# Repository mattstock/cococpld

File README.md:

cococpld
========

A complete bus interface design for the Tandy Color Computer for Arduino/AVR!

This is a combined open source/open hardware project to design a development board the Tandy/TRS-80 Color Computer.

Directories:

firmware2 - AVR Studio 6 project for a simple ROM programmer for the board.
cpld - Altera Quartus project to implement the control logic for the board.
kicad - Kicad project including the schematics and board layout.

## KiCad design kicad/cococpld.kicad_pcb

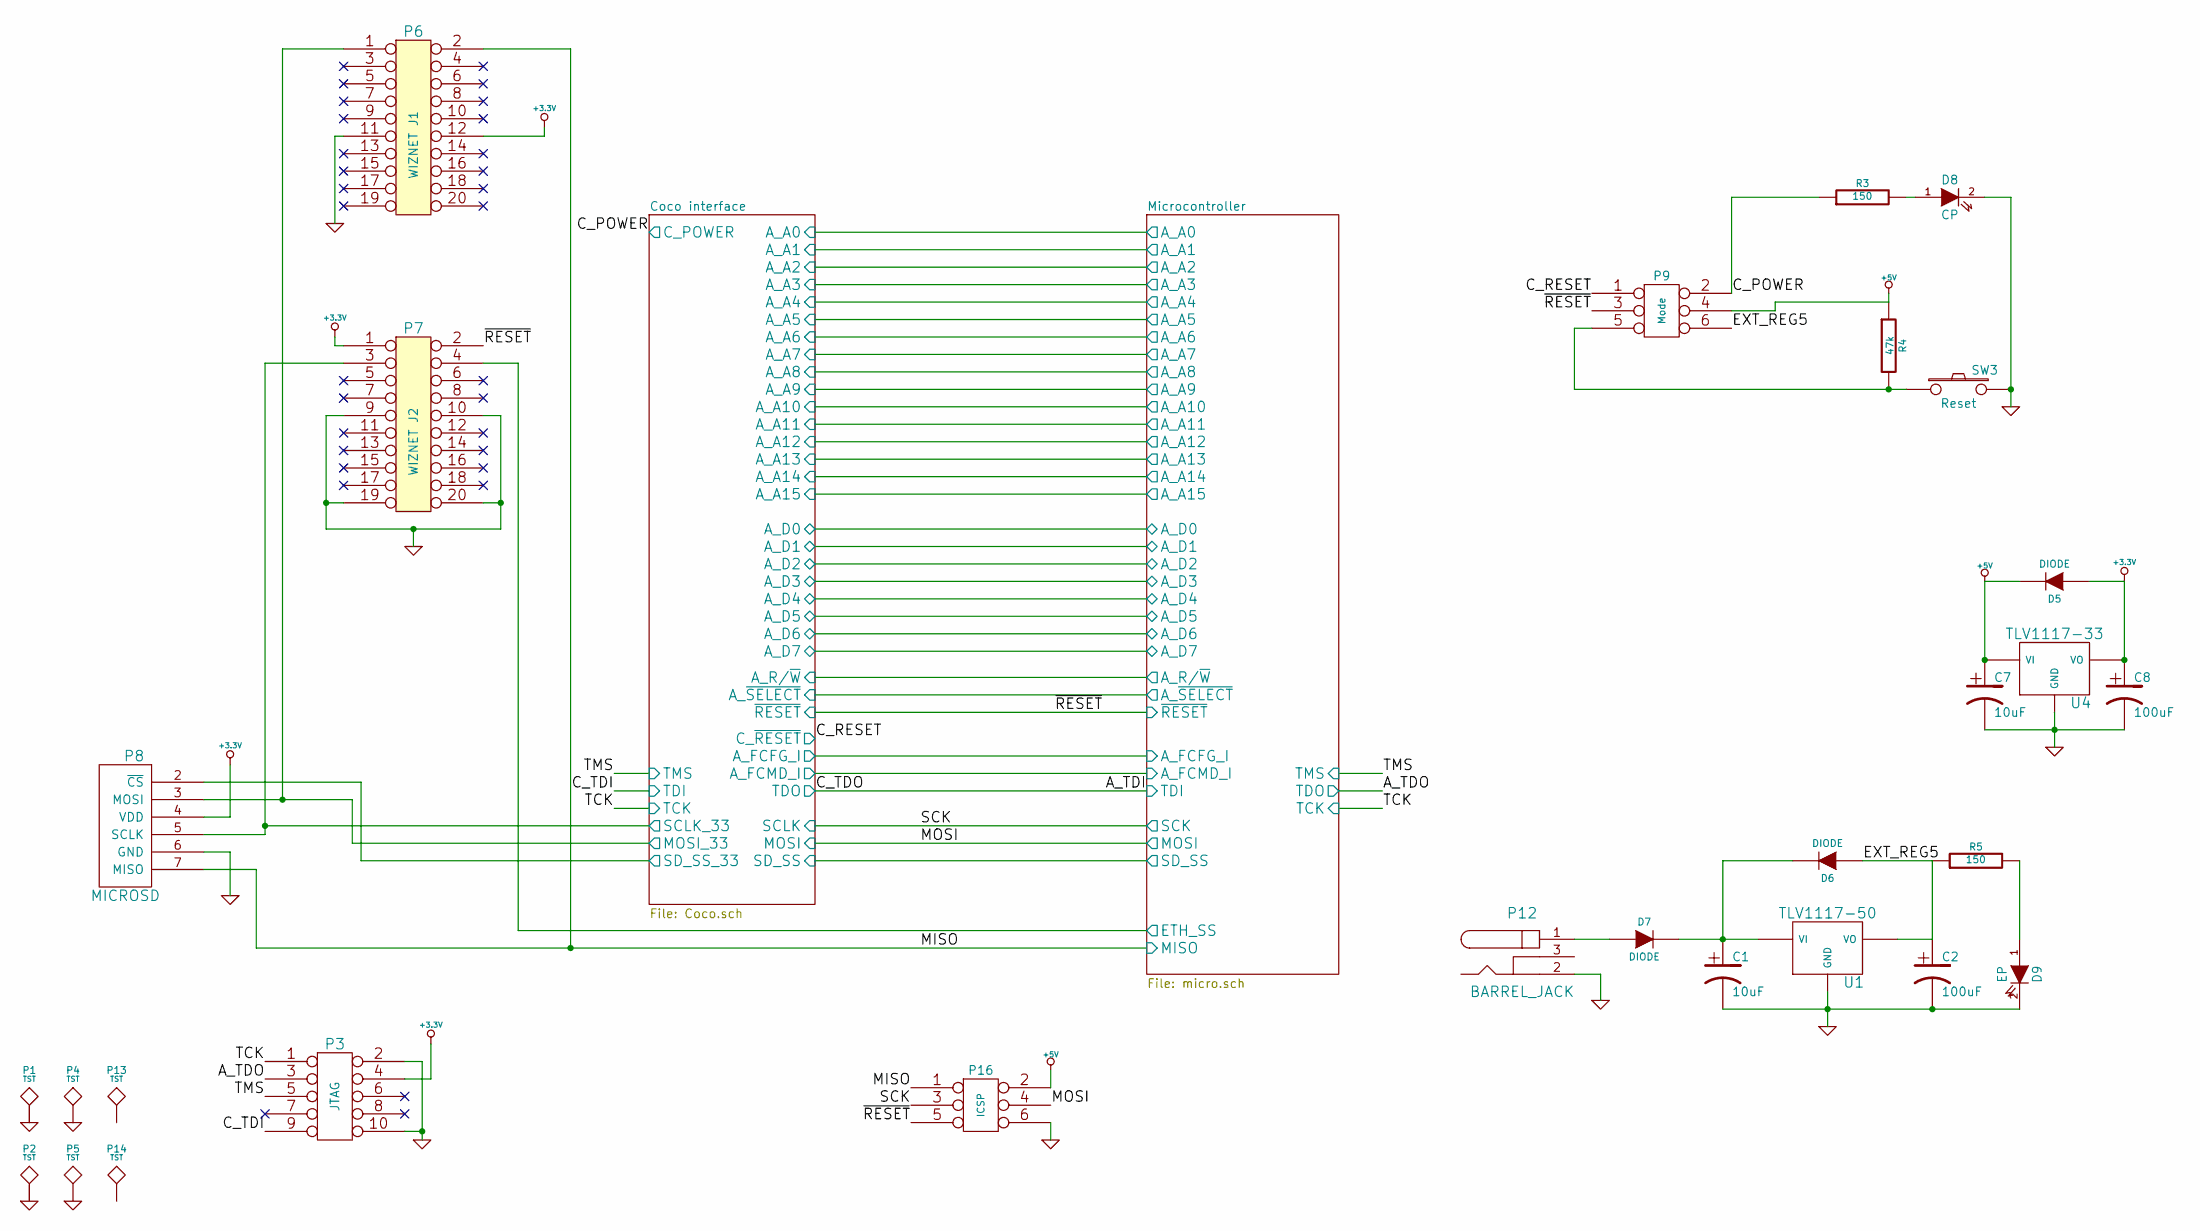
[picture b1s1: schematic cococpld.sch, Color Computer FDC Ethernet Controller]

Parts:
C1, C7: 10uF
C2, C8: 100uF
D5, D6, D7: DIODE
D8: CP
D9: EP
P1, P2, P4, P5, P13, P14: TST
P3: JTAG
P6: WIZNET J1
P7: WIZNET J2
P8: MICROSD
P9: Mode
P12: BARREL_JACK
P16: ICSP
R3, R5: 150
R4: 47k
SW3: Reset
U1: TLV1117-50
U4: TLV1117-33

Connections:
+3.3V: C8.1, D5.1 (A), P3.4, P6.12, P7.1, P8.4 (VDD), U4.2 (VO); also elsewhere on the board
+5V: C7.1, D5.2 (K), P9.4, P16.2, R4.1, U4.3 (VI); also elsewhere on the board
/Coco interface/C_POWER: P9.2, R3.1; also elsewhere on the board
/Coco interface/C_~RESET: P9.1; also elsewhere on the board
/Coco interface/MOSI: P16.4; also elsewhere on the board
/Coco interface/MOSI_33: P6.1, P8.3 (MOSI); also elsewhere on the board
/Coco interface/SCLK_33: P7.3, P8.5 (SCLK); also elsewhere on the board
/Coco interface/SD_SS_33: P8.2 (~CS); also elsewhere on the board
/Coco interface/TCK: P3.1; also elsewhere on the board
/Coco interface/TDI: P3.9; also elsewhere on the board
/Coco interface/TMS: P3.5; also elsewhere on the board
/Coco interface/~RESET: P7.2, P9.3, P16.5; also elsewhere on the board
/EXT_REG5: C2.1, D6.1 (A), P9.6, R5.1, U1.2 (VO)
/Microcontroller/ETH_SS: P7.4; also elsewhere on the board
/Microcontroller/MISO: P6.2, P8.7 (MISO), P16.1; also elsewhere on the board
/Microcontroller/SCK: P16.3; also elsewhere on the board
/Microcontroller/TDO: P3.3; also elsewhere on the board
GND: C1.2, C2.2, C7.2, C8.2, D8.2 (K), D9.2 (K), P1.1, P2.1, P3.2, P3.10, P4.1, P5.1, P6.11, P7.9, P7.10, P7.19, P7.20, P8.6 (GND), P12.2, P16.6, SW3.2, U1.1 (GND), U4.1 (GND); also elsewhere on the board
unnamed: C1.1, D6.2 (K), D7.2 (K), U1.3 (VI)
unnamed: D7.1 (A), P12.1
unnamed: D9.1 (A), R5.2
unnamed: D8.1 (A), R3.2
unnamed: P9.5, R4.2, SW3.1

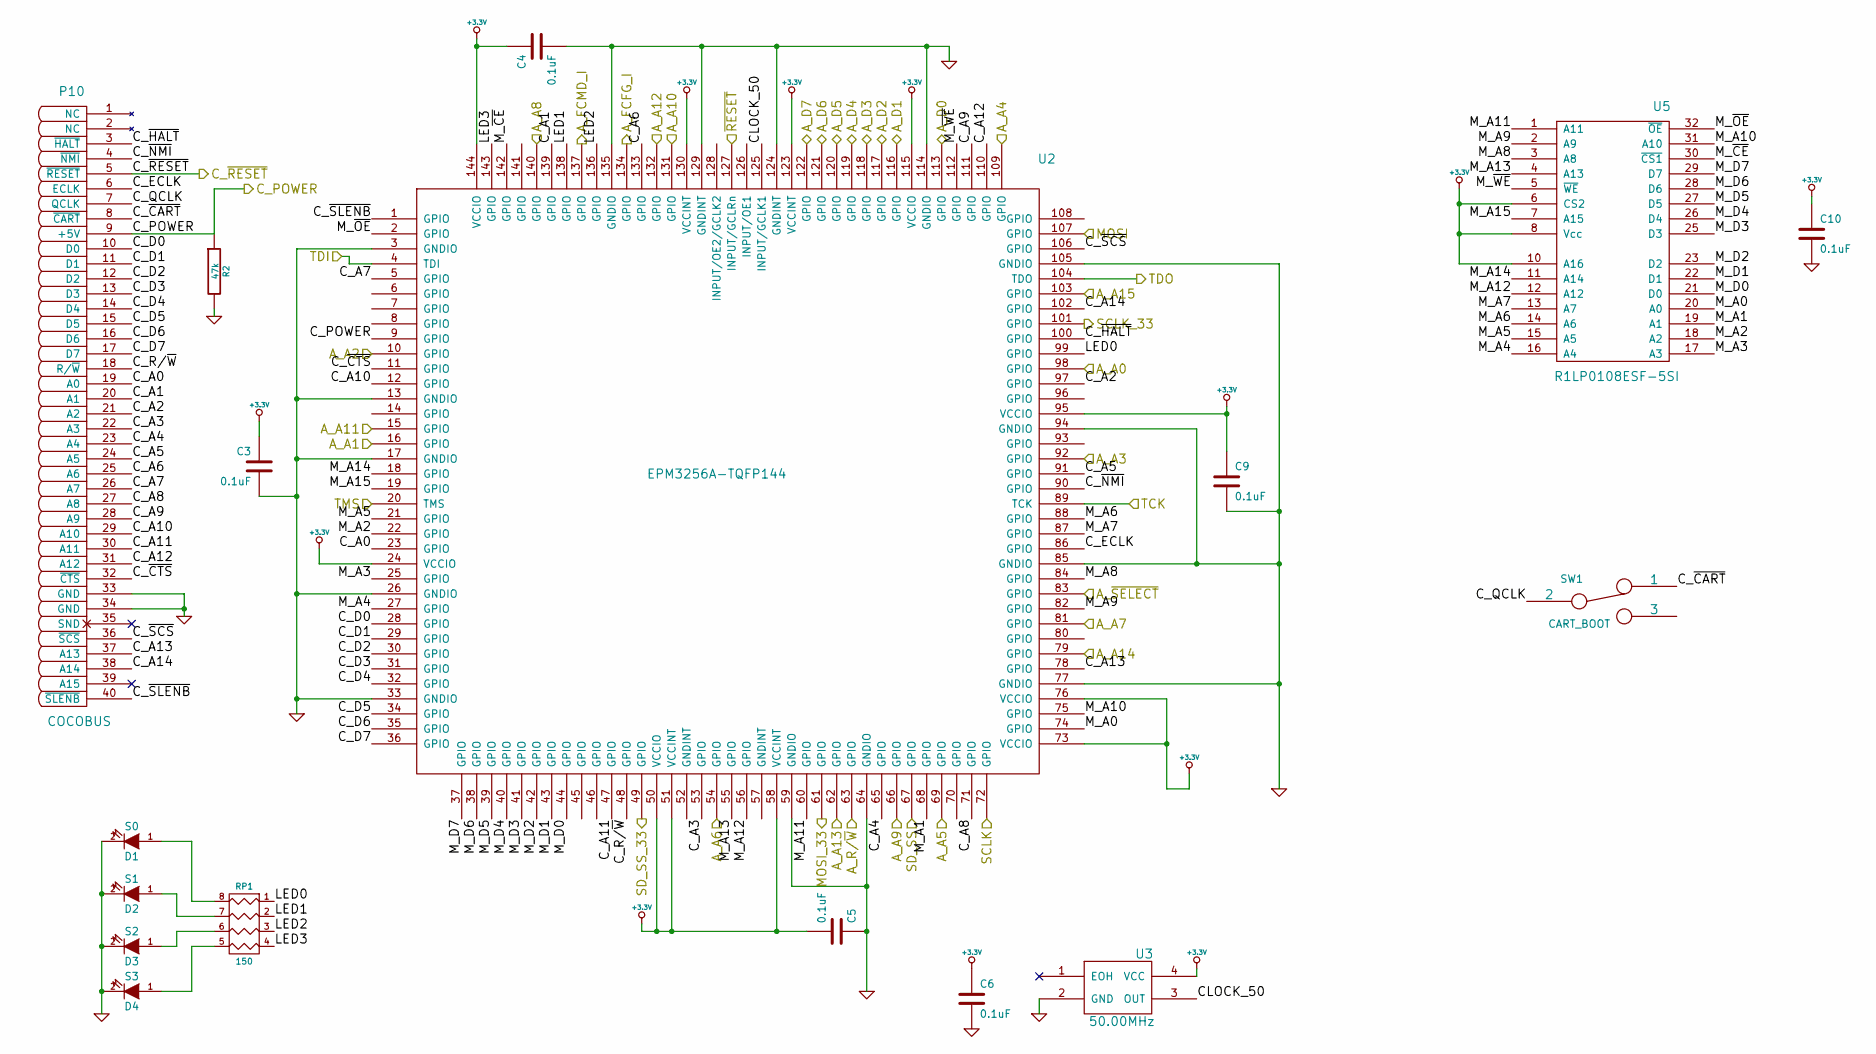
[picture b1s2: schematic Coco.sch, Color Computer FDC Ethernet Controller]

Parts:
C3, C4, C5, C6, C9, C10: 0.1uF
D1: S0
D2: S1
D3: S2
D4: S3
P10: COCOBUS
R2: 47k
RP1: 150
SW1: CART_BOOT
U2: EPM3256A-TQFP144
U3: 50.00MHz
U5: R1LP0108ESF-5SI

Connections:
+3.3V: C3.1, C4.1, C5.2, C6.1, C9.1, C10.1, U2.24 (VCCIO), U2.50 (VCCIO), U2.51 (VCCINT), U2.58 (VCCINT), U2.73 (VCCIO), U2.76 (VCCIO), U2.95 (VCCIO), U2.115 (VCCIO), U2.123 (VCCINT), U2.130 (VCCINT), U2.144 (VCCIO), U3.4 (VCC), U5.6 (CS2), U5.8 (Vcc), U5.10 (A16); also elsewhere on the board
/Coco interface/A_A0: U2.98 (GPIO); also elsewhere on the board
/Coco interface/A_A1: U2.16 (GPIO); also elsewhere on the board
/Coco interface/A_A2: U2.10 (GPIO); also elsewhere on the board
/Coco interface/A_A3: U2.92 (GPIO); also elsewhere on the board
/Coco interface/A_A4: U2.109 (GPIO); also elsewhere on the board
/Coco interface/A_A5: U2.69 (GPIO); also elsewhere on the board
/Coco interface/A_A6: U2.54 (GPIO); also elsewhere on the board
/Coco interface/A_A7: U2.81 (GPIO); also elsewhere on the board
/Coco interface/A_A8: U2.140 (GPIO); also elsewhere on the board
/Coco interface/A_A9: U2.66 (GPIO); also elsewhere on the board
/Coco interface/A_A10: U2.131 (GPIO); also elsewhere on the board
/Coco interface/A_A11: U2.15 (GPIO); also elsewhere on the board
/Coco interface/A_A12: U2.132 (GPIO); also elsewhere on the board
/Coco interface/A_A13: U2.62 (GPIO); also elsewhere on the board
/Coco interface/A_A14: U2.79 (GPIO); also elsewhere on the board
/Coco interface/A_A15: U2.103 (GPIO); also elsewhere on the board
/Coco interface/A_D0: U2.113 (GPIO); also elsewhere on the board
/Coco interface/A_D1: U2.116 (GPIO); also elsewhere on the board
/Coco interface/A_D2: U2.117 (GPIO); also elsewhere on the board
/Coco interface/A_D3: U2.118 (GPIO); also elsewhere on the board
/Coco interface/A_D4: U2.119 (GPIO); also elsewhere on the board
/Coco interface/A_D5: U2.120 (GPIO); also elsewhere on the board
/Coco interface/A_D6: U2.121 (GPIO); also elsewhere on the board
/Coco interface/A_D7: U2.122 (GPIO); also elsewhere on the board
/Coco interface/A_FCFG_I: U2.134 (GPIO); also elsewhere on the board
/Coco interface/A_FCMD_I: U2.137 (GPIO); also elsewhere on the board
/Coco interface/A_R/~W: U2.63 (GPIO); also elsewhere on the board
/Coco interface/A_~SELECT: U2.83 (GPIO); also elsewhere on the board
/Coco interface/CLOCK_50: U2.125 (INPUT/GCLK1), U3.3 (OUT)
/Coco interface/C_A0: P10.19 (A0), U2.23 (GPIO)
/Coco interface/C_A1: P10.20 (A1), U2.139 (GPIO)
/Coco interface/C_A2: P10.21 (A2), U2.97 (GPIO)
/Coco interface/C_A3: P10.22 (A3), U2.53 (GPIO)
/Coco interface/C_A4: P10.23 (A4), U2.65 (GPIO)
/Coco interface/C_A5: P10.24 (A5), U2.91 (GPIO)
/Coco interface/C_A6: P10.25 (A6), U2.133 (GPIO)
/Coco interface/C_A7: P10.26 (A7), U2.5 (GPIO)
/Coco interface/C_A8: P10.27 (A8), U2.71 (GPIO)
/Coco interface/C_A9: P10.28 (A9), U2.111 (GPIO)
/Coco interface/C_A10: P10.29 (A10), U2.12 (GPIO)
/Coco interface/C_A11: P10.30 (A11), U2.47 (GPIO)
/Coco interface/C_A12: P10.31 (A12), U2.110 (GPIO)
/Coco interface/C_A13: P10.37 (A13), U2.78 (GPIO)
/Coco interface/C_A14: P10.38 (A14), U2.102 (GPIO)
/Coco interface/C_D0: P10.10 (D0), U2.28 (GPIO)
/Coco interface/C_D1: P10.11 (D1), U2.29 (GPIO)
/Coco interface/C_D2: P10.12 (D2), U2.30 (GPIO)
/Coco interface/C_D3: P10.13 (D3), U2.31 (GPIO)
/Coco interface/C_D4: P10.14 (D4), U2.32 (GPIO)
/Coco interface/C_D5: P10.15 (D5), U2.34 (GPIO)
/Coco interface/C_D6: P10.16 (D6), U2.35 (GPIO)
/Coco interface/C_D7: P10.17 (D7), U2.36 (GPIO)
/Coco interface/C_ECLK: P10.6 (ECLK), U2.86 (GPIO)
/Coco interface/C_POWER: P10.9 (+5V), R2.1, U2.9 (GPIO); also elsewhere on the board
/Coco interface/C_QCLK: P10.7 (QCLK), SW1.2
/Coco interface/C_R/~W: P10.18 (R/~W), U2.48 (GPIO)
/Coco interface/C_~CART: P10.8 (~CART), SW1.1
/Coco interface/C_~CTS: P10.32 (~CTS), U2.11 (GPIO)
/Coco interface/C_~HALT: P10.3 (~HALT), U2.100 (GPIO)
/Coco interface/C_~NMI: P10.4 (~NMI), U2.90 (GPIO)
/Coco interface/C_~RESET: P10.5 (~RESET); also elsewhere on the board
/Coco interface/C_~SCS: P10.36 (~SCS), U2.106 (GPIO)
/Coco interface/C_~SLENB: P10.40 (~SLENB), U2.1 (GPIO)
/Coco interface/LED0: RP1.1, U2.99 (GPIO)
/Coco interface/LED1: RP1.2, U2.138 (GPIO)
/Coco interface/LED2: RP1.3, U2.136 (GPIO)
/Coco interface/LED3: RP1.4, U2.143 (GPIO)
/Coco interface/MOSI: U2.107 (GPIO); also elsewhere on the board
/Coco interface/MOSI_33: U2.61 (GPIO); also elsewhere on the board
/Coco interface/M_A0: U2.74 (GPIO), U5.20 (A0)
/Coco interface/M_A1: U2.68 (GPIO), U5.19 (A1)
/Coco interface/M_A2: U2.22 (GPIO), U5.18 (A2)
/Coco interface/M_A3: U2.25 (GPIO), U5.17 (A3)
/Coco interface/M_A4: U2.27 (GPIO), U5.16 (A4)
/Coco interface/M_A5: U2.21 (GPIO), U5.15 (A5)
/Coco interface/M_A6: U2.88 (GPIO), U5.14 (A6)
/Coco interface/M_A7: U2.87 (GPIO), U5.13 (A7)
/Coco interface/M_A8: U2.84 (GPIO), U5.3 (A8)
/Coco interface/M_A9: U2.82 (GPIO), U5.2 (A9)
/Coco interface/M_A10: U2.75 (GPIO), U5.31 (A10)
/Coco interface/M_A11: U2.60 (GPIO), U5.1 (A11)
/Coco interface/M_A12: U2.56 (GPIO), U5.12 (A12)
/Coco interface/M_A13: U2.55 (GPIO), U5.4 (A13)
/Coco interface/M_A14: U2.18 (GPIO), U5.11 (A14)
/Coco interface/M_A15: U2.19 (GPIO), U5.7 (A15)
/Coco interface/M_D0: U2.44 (GPIO), U5.21 (D0)
/Coco interface/M_D1: U2.43 (GPIO), U5.22 (D1)
/Coco interface/M_D2: U2.42 (GPIO), U5.23 (D2)
/Coco interface/M_D3: U2.41 (GPIO), U5.25 (D3)
/Coco interface/M_D4: U2.40 (GPIO), U5.26 (D4)
/Coco interface/M_D5: U2.39 (GPIO), U5.27 (D5)
/Coco interface/M_D6: U2.38 (GPIO), U5.28 (D6)
/Coco interface/M_D7: U2.37 (GPIO), U5.29 (D7)
/Coco interface/M_~CE: U2.142 (GPIO), U5.30 (~CS1)
/Coco interface/M_~OE: U2.2 (GPIO), U5.32 (~OE)
/Coco interface/M_~WE: U2.112 (GPIO), U5.5 (~WE)
/Coco interface/SCLK_33: U2.101 (GPIO); also elsewhere on the board
/Coco interface/SD_SS: U2.67 (GPIO); also elsewhere on the board
/Coco interface/SD_SS_33: U2.49 (GPIO); also elsewhere on the board
/Coco interface/TCK: U2.89 (TCK); also elsewhere on the board
/Coco interface/TDI: U2.4 (TDI); also elsewhere on the board
/Coco interface/TMS: U2.20 (TMS); also elsewhere on the board
/Coco interface/~RESET: U2.127 (INPUT/GCLRn); also elsewhere on the board
/Microcontroller/SCK: U2.72 (GPIO); also elsewhere on the board
/Microcontroller/TDI: U2.104 (TDO); also elsewhere on the board
GND: C3.2, C4.2, C5.1, C6.2, C9.2, C10.2, D1.2 (K), D2.2 (K), D3.2 (K), D4.2 (K), P10.33 (GND), P10.34 (GND), R2.2, U2.3 (GNDIO), U2.13 (GNDIO), U2.17 (GNDIO), U2.26 (GNDIO), U2.33 (GNDIO), U2.59 (GNDIO), U2.64 (GNDIO), U2.77 (GNDIO), U2.85 (GNDIO), U2.94 (GNDIO), U2.105 (GNDIO), U2.114 (GNDIO), U2.124 (GNDINT), U2.129 (GNDINT), U2.135 (GNDIO), U3.2 (GND), U5.24 (GND); also elsewhere on the board
unnamed: D3.1 (A), RP1.6 (R3)
unnamed: D1.1 (A), RP1.8 (R1)
unnamed: D4.1 (A), RP1.5 (R4)
unnamed: D2.1 (A), RP1.7 (R2)

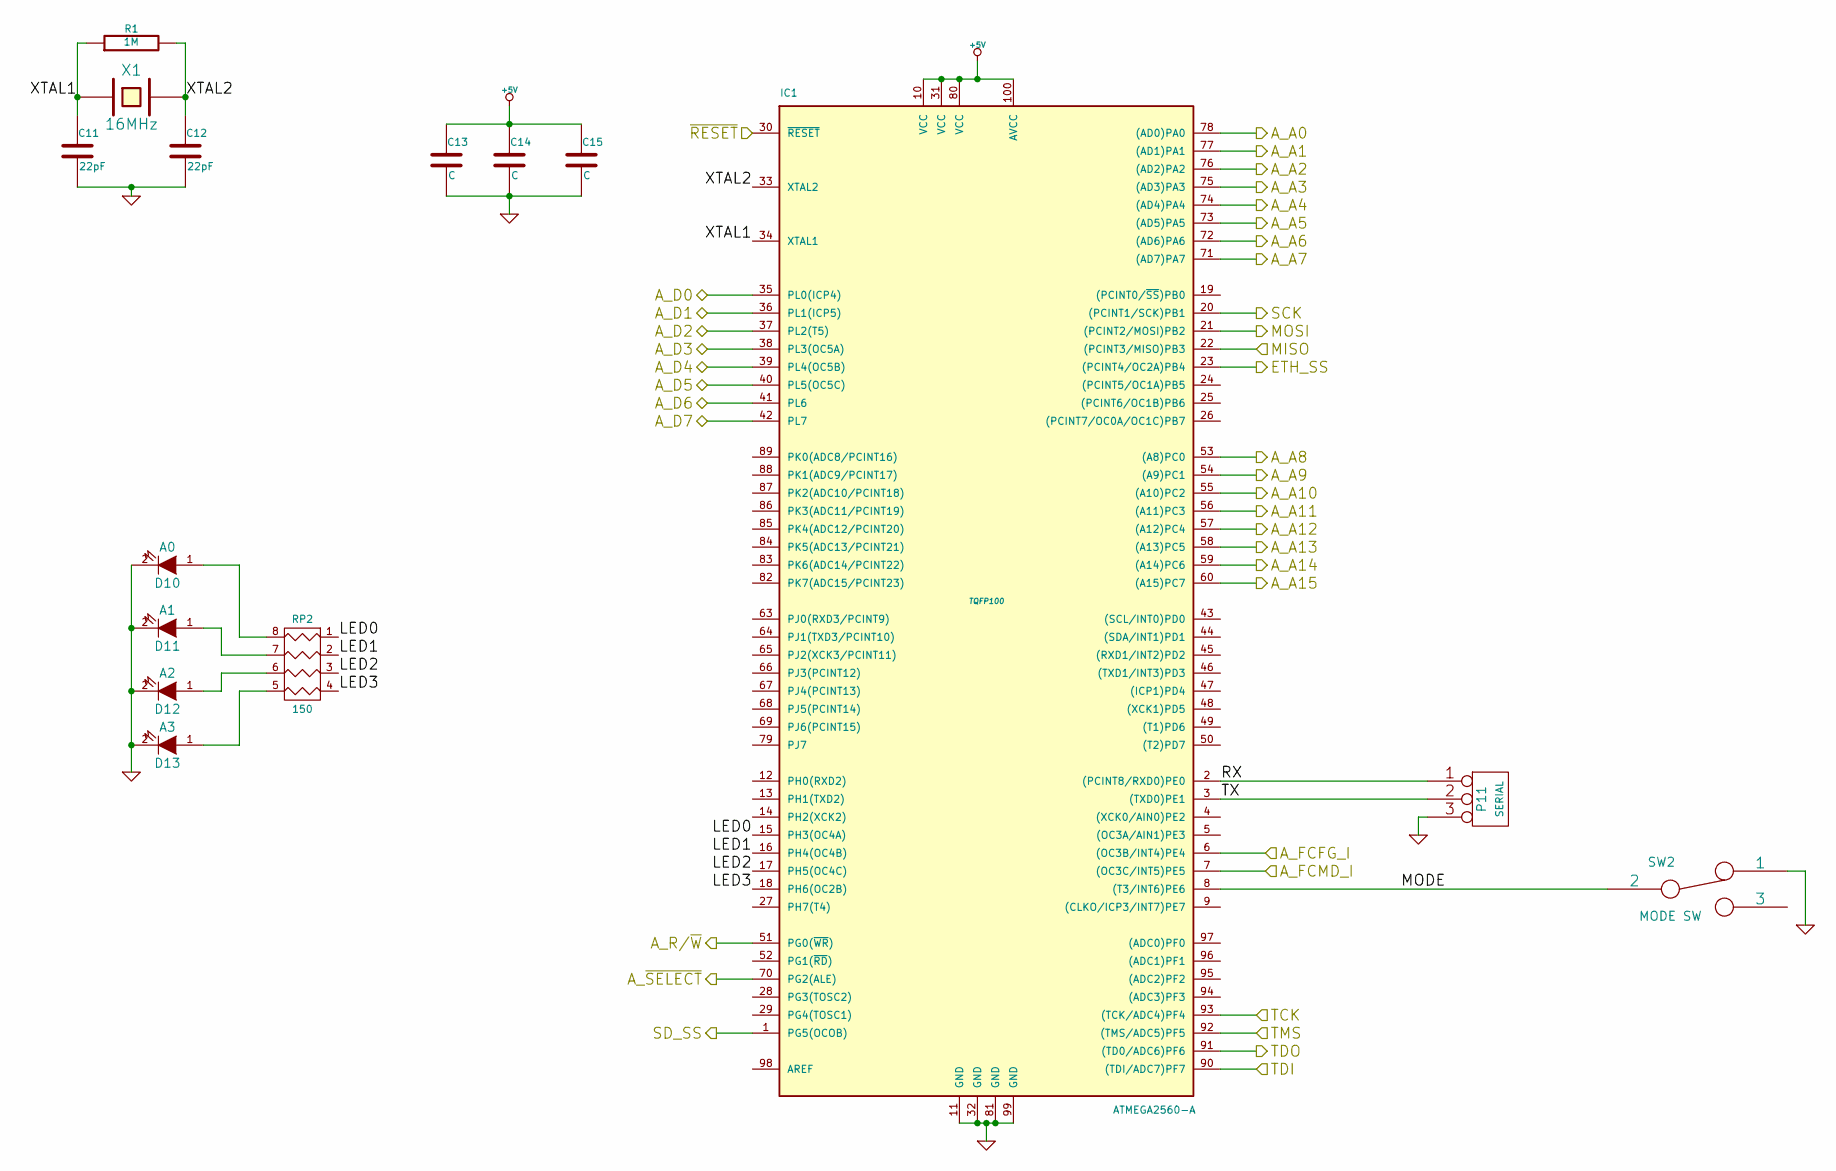
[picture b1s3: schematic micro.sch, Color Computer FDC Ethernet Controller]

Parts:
C11, C12: 22pF
C13, C14, C15: C
D10: A0
D11: A1
D12: A2
D13: A3
IC1: ATMEGA2560-A; TQFP100
P11: SERIAL
R1: 1M
RP2: 150
SW2: MODE SW
X1: 16MHz

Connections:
+5V: C13.1, C14.1, C15.1, IC1.10 (VCC), IC1.31 (VCC), IC1.80 (VCC), IC1.100 (AVCC); also elsewhere on the board
/Coco interface/A_A0: IC1.78 ((AD0)PA0); also elsewhere on the board
/Coco interface/A_A1: IC1.77 ((AD1)PA1); also elsewhere on the board
/Coco interface/A_A2: IC1.76 ((AD2)PA2); also elsewhere on the board
/Coco interface/A_A3: IC1.75 ((AD3)PA3); also elsewhere on the board
/Coco interface/A_A4: IC1.74 ((AD4)PA4); also elsewhere on the board
/Coco interface/A_A5: IC1.73 ((AD5)PA5); also elsewhere on the board
/Coco interface/A_A6: IC1.72 ((AD6)PA6); also elsewhere on the board
/Coco interface/A_A7: IC1.71 ((AD7)PA7); also elsewhere on the board
/Coco interface/A_A8: IC1.53 ((A8)PC0); also elsewhere on the board
/Coco interface/A_A9: IC1.54 ((A9)PC1); also elsewhere on the board
/Coco interface/A_A10: IC1.55 ((A10)PC2); also elsewhere on the board
/Coco interface/A_A11: IC1.56 ((A11)PC3); also elsewhere on the board
/Coco interface/A_A12: IC1.57 ((A12)PC4); also elsewhere on the board
/Coco interface/A_A13: IC1.58 ((A13)PC5); also elsewhere on the board
/Coco interface/A_A14: IC1.59 ((A14)PC6); also elsewhere on the board
/Coco interface/A_A15: IC1.60 ((A15)PC7); also elsewhere on the board
/Coco interface/A_D0: IC1.35 (PL0(ICP4)); also elsewhere on the board
/Coco interface/A_D1: IC1.36 (PL1(ICP5)); also elsewhere on the board
/Coco interface/A_D2: IC1.37 (PL2(T5)); also elsewhere on the board
/Coco interface/A_D3: IC1.38 (PL3(OC5A)); also elsewhere on the board
/Coco interface/A_D4: IC1.39 (PL4(OC5B)); also elsewhere on the board
/Coco interface/A_D5: IC1.40 (PL5(OC5C)); also elsewhere on the board
/Coco interface/A_D6: IC1.41 (PL6); also elsewhere on the board
/Coco interface/A_D7: IC1.42 (PL7); also elsewhere on the board
/Coco interface/A_FCFG_I: IC1.6 ((OC3B/INT4)PE4); also elsewhere on the board
/Coco interface/A_FCMD_I: IC1.7 ((OC3C/INT5)PE5); also elsewhere on the board
/Coco interface/A_R/~W: IC1.51 (PG0(~WR~)); also elsewhere on the board
/Coco interface/A_~SELECT: IC1.70 (PG2(ALE)); also elsewhere on the board
/Coco interface/MOSI: IC1.21 ((PCINT2/MOSI)PB2); also elsewhere on the board
/Coco interface/SD_SS: IC1.1 (PG5(OCOB)); also elsewhere on the board
/Coco interface/TCK: IC1.93 ((TCK/ADC4)PF4); also elsewhere on the board
/Coco interface/TMS: IC1.92 ((TMS/ADC5)PF5); also elsewhere on the board
/Coco interface/~RESET: IC1.30 (~RESET); also elsewhere on the board
/Microcontroller/ETH_SS: IC1.23 ((PCINT4/OC2A)PB4); also elsewhere on the board
/Microcontroller/LED0: IC1.15 (PH3(OC4A)), RP2.1
/Microcontroller/LED1: IC1.16 (PH4(OC4B)), RP2.2
/Microcontroller/LED2: IC1.17 (PH5(OC4C)), RP2.3
/Microcontroller/LED3: IC1.18 (PH6(OC2B)), RP2.4
/Microcontroller/MISO: IC1.22 ((PCINT3/MISO)PB3); also elsewhere on the board
/Microcontroller/MODE: IC1.8 ((T3/INT6)PE6), SW2.2
/Microcontroller/RX: IC1.2 ((PCINT8/RXD0)PE0), P11.1
/Microcontroller/SCK: IC1.20 ((PCINT1/SCK)PB1); also elsewhere on the board
/Microcontroller/TDI: IC1.90 ((TDI/ADC7)PF7); also elsewhere on the board
/Microcontroller/TDO: IC1.91 ((TD0/ADC6)PF6); also elsewhere on the board
/Microcontroller/TX: IC1.3 ((TXD0)PE1), P11.2 (PM)
/Microcontroller/XTAL1: C11.1, IC1.34 (XTAL1), R1.1, X1.1
/Microcontroller/XTAL2: C12.1, IC1.33 (XTAL2), R1.2, X1.2
GND: C11.2, C12.2, C13.2, C14.2, C15.2, D10.2 (K), D11.2 (K), D12.2 (K), D13.2 (K), IC1.11 (GND), IC1.32 (GND), IC1.81 (GND), IC1.99 (GND), P11.3, SW2.1; also elsewhere on the board
unnamed: D13.1 (A), RP2.5 (R4)
unnamed: D12.1 (A), RP2.6 (R3)
unnamed: D10.1 (A), RP2.8 (R1)
unnamed: D11.1 (A), RP2.7 (R2)

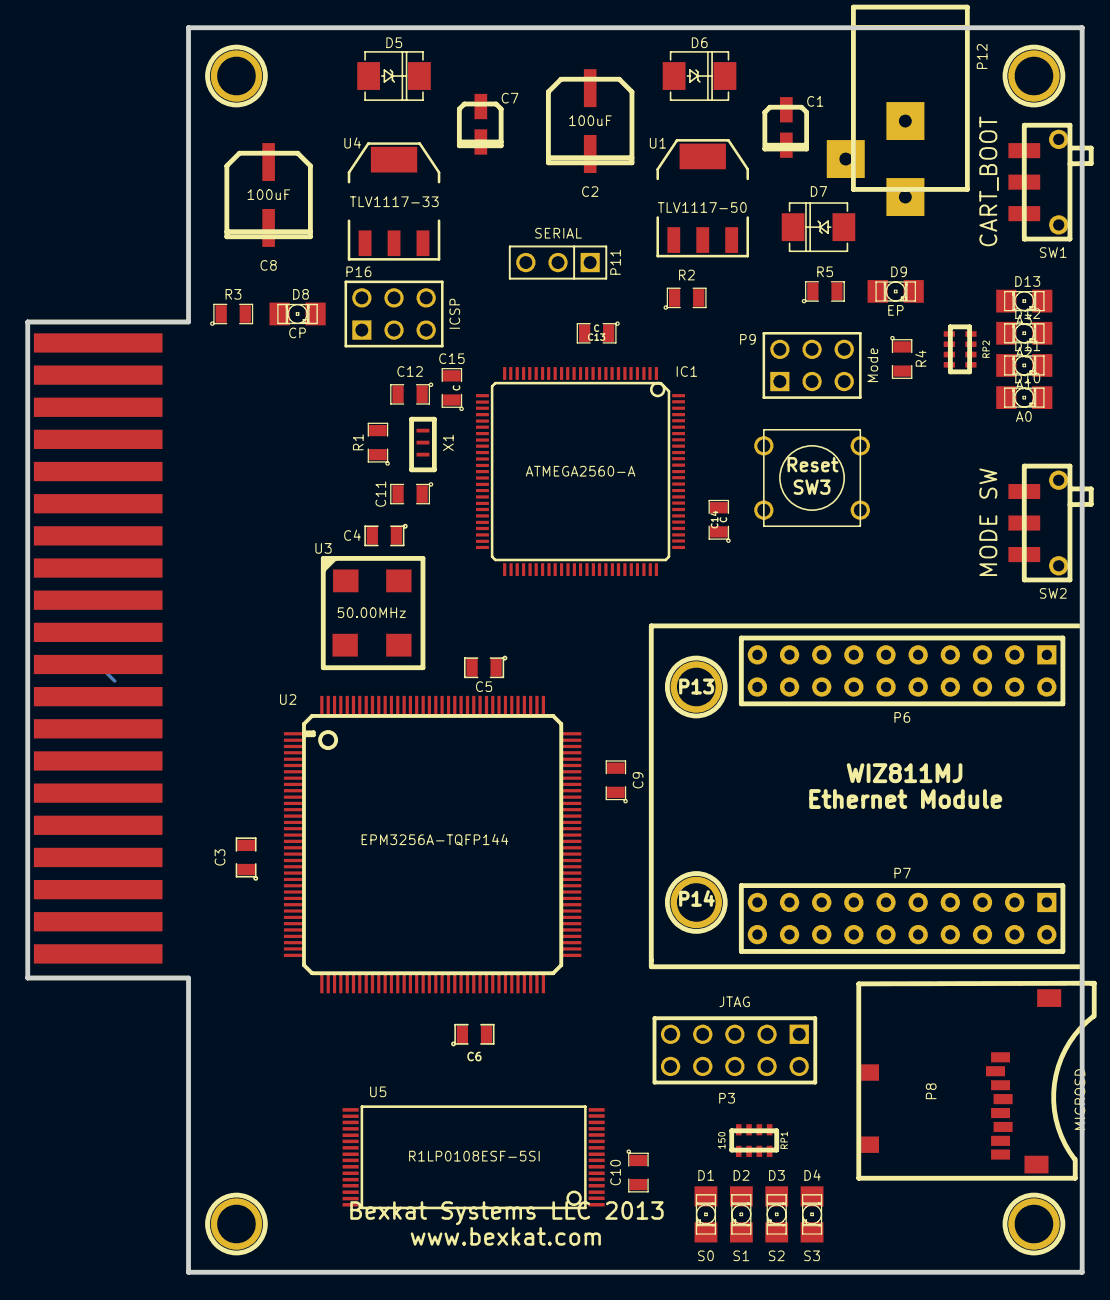
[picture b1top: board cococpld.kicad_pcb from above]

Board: 2 copper layers, 83.3 x 98.3 mm, 60 parts (0 on the bottom side), 134 nets.

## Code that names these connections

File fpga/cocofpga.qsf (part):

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set_location_assignment PIN_W21 -to LEDG[5]
set_location_assignment PIN_Y22 -to LEDG[6]
set_location_assignment PIN_Y21 -to LEDG[7]
set_location_assignment PIN_L1 -to clock_50
set_location_assignment PIN_AA3 -to sram_addrbus[0]
set_location_assignment PIN_Y5 -to sram_addrbus[17]
set_location_assignment PIN_Y6 -to sram_addrbus[16]
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set_location_assignment PIN_T8 -to sram_oe_n
set_location_assignment PIN_W7 -to sram_ub_n
set_location_assignment PIN_AA10 -to sram_we_n
set_location_assignment PIN_B13 -to c_eclk
set_location_assignment PIN_A14 -to c_qclk
set_location_assignment PIN_B14 -to c_rw
set_location_assignment PIN_B15 -to c_scs_n
set_location_assignment PIN_L18 -to c_slenb_n
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
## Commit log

2013-05-05 baseline for v1.2 hardware config
2013-05-05 start of integration of common bus into CPLD
2013-05-06 updates to local project paths
2013-05-06 add README
2013-05-06 I have no idea
2013-05-07 updates to bus interface for v1.2 HW
2013-05-07 added board routing
2013-05-07 implement control logic for register memory
2013-05-07 small
2013-05-08 start to the SPI mods
2013-05-13 fixes to een ordering
2013-05-21 rearranging libraries
2013-05-21 working against fpga
2013-05-22 first shot as fitting the logic into CPLD
2013-05-23 jammed SPI stuff into CPLD
2013-05-23 start of new schematic and board layout
2013-05-24 fit all of the control code, added dirty indicator and external interrupt.
2013-05-24 revamped schematic
2013-05-24 new board layout
2013-05-26 updates for v1.3 board
2013-05-26 experiments with different hardware configurations. This one moves everything into the chip except memory.
2013-05-26 minor edits
2013-05-30 move fpga test code into cpld model
2013-05-30 one big happy solution with multiple projects for the mega2560
2013-05-31 start to change memory and bus config
2013-06-04 some additional bus testing code
2013-06-07 design ported from FPGA
2013-06-08 firmware project fixes, verilog fits, HW design in progress
2013-06-09 mostly setup verilog for CPLD
2013-06-09 v1.3 hardware design is completely busted - bad SRAM footprint
2013-06-09 v1.4 HW design
2013-06-09 v1.4 schematic and board with corrections
2013-06-09 v1.4 verilog with correct pinout
2013-06-15 update to v13 of quartus
2013-06-15 solution now references several sub-projects for each of the Arduino libraries. Kept outside of this build tree.
2013-06-15 additional updates for quartus v13
2013-06-15 Configured to work with MEGA ADK board and ethernet/SDcard shield for convenience. Moved all SPI select pins (lots of devices now) into busio.h
2013-06-24 mostly working FDC model. Need to work out sector reads
2013-06-26 fixed most of the bus interactions, CRC, etc.
2013-07-01 latest attempt at working fdc
2013-07-04 Completely working FDC code
2013-07-04 Addition of Ethernet library
2013-07-04 these too
2013-07-04 incorporating working control code, without ethernet support
2013-07-08 refactored disk code - still working on RBF format and switching between disk formats. Reads config from setup file. CPLD code ported from FPGA but HW design still in progress. Schematic in progress,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
2013-07-15 refactoring to support multiple virtual disk formats and config file
2013-07-16 more changes
2013-07-17 Refactors disk image code to better support vitrual disk images
2013-07-17 mostly working virtual disk directory listing
2013-07-18 removed LCD support, direct boot into fdc mode (for now), and reorganized the virtual drives to better fit the expected hardware behaviours.
2013-07-18 Updated to new FPGA logic
2013-07-20 Virtual directory working, memory corruption problem fixed.
2013-07-21 Cleaned up CocoImage type to simplify
2013-07-21 odd issues with support libraries now... May be due to C/C++ standard?
2013-07-21 still working with some of the changes applied
2013-07-22 fixed errant missing null assignment. Need to sort out out DSKI$ works in coco
2013-07-31 added microsd and ethernet chip to design
2013-08-04 hardware prototype for v2.0 board
2013-08-08 some changes
2013-08-12 datestamp?
2013-08-20 start of additional goodness and fixes
2013-08-20 initial pass for v2.1 board layout
2013-08-21 initial working set for v2.0 hardware. Need to convert bus io to parallel instead of SPI.
2013-08-21 eliminated header since JTAG chaining is confirmed to work. Also drafted changes to firmware to support parallel mode I/O to CPLD instead of SPI as well as pure ROM mode.
2013-08-22 playing with the led outputs
2013-08-22 new board route
2013-08-22 testing support
2013-08-23 fixed memory storage instructions for fdc mode
2013-08-26 working implementation at hardware level using v2.0 HW. There are still some timing issues for the disk controller IO that need to be resolved as well as some startup issues to test. HALT is enabled 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
2013-08-26 first draft of v2.1 hardware. Added some addition diagnostic leds, power indicators, and a separate SPI interface for the 5v side. Maybe add support for external LCD?
2013-08-28 minor project changes
2013-08-28 some lib changes
2013-08-30 added in some of the simulation branch changes but still using v2.0 pinout
2013-08-30 more timing constraints
2013-09-10 possible v2.1 design changes
2013-09-10 make halt a wire instead of a register, and increase time delay for SRAM since the memory is 55ns. Pinout needs to change.
2013-09-10 some additional adjustments to parallel IO controls, some debugging.
2013-09-13 rework for interrupt handler
2013-09-16 small change
2013-09-30 adding interrupt handlers, before starting to heavily optimize
2013-10-12 still not working, buy planning to start digging into interrupt handling code more completely on the Arduino end.
2013-10-14 moving to makefiles and linux based dev environment
2013-10-14 more cleaning
2013-10-14 the whole thing seems to build
2013-10-15 small fixes
2013-10-15 cbi and sbi are deprecated
2013-10-16 formatting and fixing a big sector read memory leak
2013-10-16 mostly formatting changes
2013-10-19 some more optimizations
2013-10-20 changed interrupts to use falling edge to better function with AVR systems
2013-10-20 invert iterrupt logic
2013-10-20 recoded to hold all FDC registers in CPLD. The reaon to keep them in SRAM is gone now that we have a large CPLD. Still need to work on pin assignments and optimization.
2013-10-22 reconfig to change register mapping logic. Add atomic blocks to prevent some nasty side effects when accessing memory from avr.
2013-10-23 small improvement of error message.
2013-10-23 Revert "small improvement of error message."
    This reverts commit 8b7cbec9f7246a75b7ae257e858cff8cba9ada3d.
2013-10-23 Whoops.
    Revert "Revert "small improvement of error message.""
    This reverts commit b0c30082d347fb8a64e0d93ebbbcb9c5d824ef7b.
2013-11-10 some more work
2013-11-11 more changes to use FPGA memory -- need to combine with fpga git repo somehow
2013-11-18 initial transition to FPGA
2014-01-04 Back to the future. Reboot to using the SPI interface between micro and rest of the system. Using external SRAM for the ROM and non-FDC register locations. Giving up on the standalone CPLD-based solu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
2014-01-26 added i2c LCD library and small changes to build using new SPI interface.
2014-01-26 added basic ethernet support, as well as more debug functions.
2014-01-26 fixed dependencies
2014-01-26 pull setup file from network
2014-01-31 an experiment with delayed interrupt sends for out-of-order register assignments
2014-02-01 modified CPLD config to re-support the SPI AVR interface. This 98% works for the v2.0 board. We need to bridge MISO to one of the now available pins on the CPLD.
2014-02-01 beginnings of an ethernet interface for Coco.
2014-02-02 changes to support new buffer shield
2014-02-06 forgot a bank enable
2014-02-09 added virtual MPI support - 4 rom address ranges, both hardware and software switched.
2014-03-17 added load of multiple cartridge ROMs from config file
2015-04-22 nothing important
2015-04-23 spi side working and state machine has significiantly improved timing and clarity
2015-04-24 added bank support and improved the mapping of scs registers
2015-04-27 we have a possible winner
2015-04-28 moved back to using mem for now

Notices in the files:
fpga/cocofpga.qsf:
Copyright (C) 1991-2013 Altera Corporation
